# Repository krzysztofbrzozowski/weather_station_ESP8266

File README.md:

# Weather station based on ESP8266 and BME280
## Repository Contents

- **firmware/micropython/src/** - MicroPython files deployed to the ESP8266.
- **firmware/micropython/build/** - Generated MicroPython deployment files, ignored by Git.
- **firmware/.settings** - Shared private configuration for both firmware implementations.
- **firmware/arduino/** - Native C++ firmware using Arduino, BearSSL HTTPS and LittleFS;
  see its [build and migration guide](firmware/arduino/README.md).
- **local_dev/** - CPython launcher and runtime stubs for local development.
- **platformio.sh** - Build or flash Arduino with current shared settings and image verification.

The board currently runs Arduino. For settings, builds and uploads, use the
[Arduino guide](firmware/arduino/README.md#updating-settings-and-firmware).
The deployment instructions below describe MicroPython.

## Configuration

Both implementations use the shared host configuration `firmware/.settings`.
The local MicroPython launcher reads it directly; deployment copies it to
`/.settings` on the device. Arduino's preparation tool converts it into
`/config.json` for the device. Changing the host file alone does not update the board.
If it is missing, copy `firmware/.settings.example` to that path and edit it:

```python
API_url = 'Your API url'
AUTH_TOKENS = {
    'dc:4f:22:7c:3a:fa': 'Your-token-for-first-device',
    'dc:4f:22:7c:3a:fc': 'Your-token-for-second-device',
}
BACKUP_FOLDER = 'backup_logs'
WIFI_NETWORKS = [
    {'SSID': 'Home-WiFi', 'PASSWD': 'Your-home-password'},
    {'SSID': 'Office-WiFi', 'PASSWD': 'Your-office-password'},
]
```

The file uses Python assignments and is ignored by Git. `API_url` and
`BACKUP_FOLDER` are strings. `WIFI_NETWORKS` holds 1–4 SSID/password profiles;
the legacy `SSID` and `PASSWD` strings still work when the list is absent.
The list takes precedence over legacy credentials. Each SSID is 1–32 UTF-8
bytes, each password 0–64 bytes; an empty password selects an open network.
Exact duplicate profiles are rejected; the same SSID with different passwords
is allowed.

On first use, multi-network firmware scans for configured visible SSIDs and
tries them in list order. It saves the successful profile in `/.wifi.json`,
which survives deep sleep and power loss. Later cycles try that profile first;
if connection fails they scan again and try the other visible profiles. A scan
failure falls back to direct attempts. Only a changed successful preference is
written to flash. Changing credentials/order invalidates the saved preference.
If all networks fail, measurements stay queued and discovery retries next cycle.

`AUTH_TOKENS` maps Wi-Fi station MAC
addresses to their API tokens. Each board selects its token at startup; the same
settings file/image can be used on all boards. MACs are case insensitive and
accept colons or hyphens. Use 1–100 entries and 1–256 printable ASCII characters
per token, without spaces. Duplicate MACs after normalization are rejected.

An unknown MAC leaves uploads disabled while measurements remain queued and the
normal sleep cycle continues. The console reports the missing MAC, without
printing any tokens. The legacy single-device `AUTH_TOKEN = 'Your API token'`
format still works when `AUTH_TOKENS` is absent. A present map takes precedence;
there is no fallback to another device's token.

Optional numeric controls and their defaults are:

```python
MEASUREMENT_INTERVAL_S = 300
HTTP_TIMEOUT_S = 3
BACKUP_MAX_RECORDS = 144
BACKUP_MIN_FREE_BYTES = 32768
BACKUP_MAX_SEND = 6
```

`BACKUP_FOLDER` is a single directory name. Local development uses the same file even when launched from a
different working directory; backup files still go into the simulated device
filesystem. When using `local_dev/run.py`, HTTP and Wi-Fi remain simulated.
Use `local_dev/send_test_measurements.py` below for real HTTP requests.

The measurement interval accepts 10–3600 seconds and the HTTP timeout 1–3 seconds
to stay within the ESP8266's sleep timer and fixed watchdog constraints.

## Local development

Run from the repository root with Python 3 (standard library only):

```sh
python3 local_dev/run.py
```

The launcher executes `firmware/micropython/src/boot.py` and `firmware/micropython/src/main.py`, replacing
hardware and HTTP modules with runtime stubs. It supplies fixed BME280 readings,
an ADC value and a MAC address, simulates Wi-Fi and API responses, skips
millisecond delays, and finishes when the firmware enters deep sleep.
It does not send real HTTP requests or require Wi-Fi credentials.

To simulate unavailable Wi-Fi and exercise measurement backups:

```sh
python3 local_dev/run.py --offline
python3 local_dev/run.py
```

Simulated device files are stored in `local_dev/.state/` (ignored by Git).
The second command simulates sending up to `BACKUP_MAX_SEND` pending readings.
Simulated RTC state is retained in `.state/.rtc.json` between invocations.
Use `--state-dir /path/to/directory` to choose a different device filesystem.
Adjust simulated readings in `local_dev/stubs/` as needed.

These stubs support the interfaces currently used by the application. They
replace the BME280 driver entirely and do not verify I2C communication,
sensor calibration, real API compatibility, or ESP8266 timing and power behavior.

## Deployment

Build the modules from `firmware/micropython/src/` on the computer and upload the resulting
`.mpy` files, `boot.py`, `main.py` and the private `.settings` to the ESP8266 root
as shown below. Configure Wi-Fi and API settings in `.settings`.
The `local_dev/` directory stays on the development
computer and is not deployed to the board.

Use a MicroPython build for your exact ESP8266 board with a working `urequests`
or `requests` module supporting the `timeout` argument. Do not copy the local
stubs to the board. For resilience to interrupted writes, use a LittleFS
filesystem. Connect GPIO16 to RST for timed wakeup, connect BME280 SCL to GPIO5
and SDA to GPIO4, and confirm its I2C address is `0x76`.
The existing GPIO13 charging check and ADC divider scaling are preserved;
they must match your PCB. Test a complete sleep/wake cycle on the actual board.

### 1. Install the flashing tools

The commands below use **macOS/Linux**, Python **3.10+**, and the current
`esptool` command syntax. Run them from the repository root:

```sh
python3 -m venv .venv
source .venv/bin/activate
python -m pip install --upgrade esptool mpremote
```

`esptool` installs the MicroPython interpreter; `mpremote` transfers this
project's Python files afterwards. See the official
[esptool installation guide](https://docs.espressif.com/projects/esptool/en/latest/esp8266/installation.html).

### 2. Connect the board and identify its flash size

Use a USB data cable and close other serial terminals. List connected ports:

```sh
python -m serial.tools.list_ports
```

Set the actual port shown above (the following macOS name is an example;
Linux commonly uses `/dev/ttyUSB0`):

```sh
ESP_PORT='/dev/cu.usbserial-210'
python -m esptool --chip esp8266 --port "$ESP_PORT" flash-id
```

Read `Detected flash size` before choosing a firmware variant. Boards with an
automatic reset circuit usually enter the bootloader themselves. Otherwise,
hold **FLASH/BOOT** (GPIO0 low), press and release **RST**, and retry the command.
For a bare module, pull GPIO0 to GND while resetting; release GPIO0 for normal boot.

### 3. Download the latest stable MicroPython binary

Open the official [ESP8266 firmware downloads](https://micropython.org/download/ESP8266_GENERIC/)
and choose the newest `.bin` under **Releases** for your flash size. As of
**2026-10-14**, the latest stable release is **v1.29.0 (2026-08-24)**; check that
page again when installing later.

| Detected flash | Firmware choice |
| --- | --- |
| 2–4 MiB | Standard `ESP8266_GENERIC` build |
| 1 MiB | `FLASH_1M` variant; fewer bundled modules and less buffer space |
| 512 KiB | Unsuitable for this project: the current variant has no filesystem |
| 8–16 MiB | Standard build plus the [additional RF calibration procedure](https://docs.micropython.org/en/latest/esp8266/tutorial/intro.html#boards-with-more-than-4mb-of-flash) |

Use a release build for the station. Preview builds are development snapshots.
Rename your downloaded file to `micropython-esp8266.bin` and set its path:

```sh
MICROPYTHON_BIN="$HOME/Downloads/micropython-esp8266.bin"
```

### 4. Erase the old firmware and flash MicroPython

**Erasing removes everything on the board, including `.settings` and unsent
measurements.** Save anything you need before this step. The standard procedure
below covers boards with 1–4 MiB flash:

```sh
python -m esptool --chip esp8266 --port "$ESP_PORT" erase-flash
python -m esptool --chip esp8266 --port "$ESP_PORT" --baud 460800 write-flash --flash-size detect 0x0 "$MICROPYTHON_BIN"
```

The ESP8266 image starts at **`0x0`**. Current esptool uses names such as
`write-flash` and `erase-flash`; older tutorials use underscores.
If writing is unreliable, retry at `--baud 115200`. If flashing succeeds but
MicroPython does not boot, retry with the compatibility flash mode:

```sh
python -m esptool --chip esp8266 --port "$ESP_PORT" --baud 115200 write-flash --flash-size detect --flash-mode dout 0x0 "$MICROPYTHON_BIN"
```

Release FLASH/GPIO0 and press RST after flashing. Let the first boot initialize
the filesystem, then check the interpreter:

```sh
mpremote connect "$ESP_PORT" exec "import sys; print(sys.implementation)"
```

Command references: [MicroPython ESP8266 installation](https://docs.micropython.org/en/latest/esp8266/tutorial/intro.html)
and [esptool flash commands](https://docs.espressif.com/projects/esptool/en/latest/esp8266/esptool/basic-commands.html).

### 5. Prepare settings and the HTTP library

Create `firmware/.settings` from `.settings.example` **only if it does not
already exist**, then enter the actual API and Wi-Fi settings in your editor.
Keep an existing private configuration when updating.

```sh
test -f firmware/.settings || cp firmware/.settings.example firmware/.settings
mpremote connect "$ESP_PORT" mip install requests
mpremote connect "$ESP_PORT" exec "import requests; print('HTTP library available')"
```

Installing `requests` uses the computer's Internet connection and USB transfer;
the board does not need to join Wi-Fi for this step. The firmware supports
`urequests` as well. If an older copy of `urequests.py` was previously uploaded,
update or remove that obsolete copy so it does not shadow the current library.
See [MicroPython package installation](https://docs.micropython.org/en/latest/reference/packages.html#installing-packages-with-mpremote).

### 6. Upload the station code

ESP8266 has limited RAM. Compiling all source modules on the device can fail
with `MemoryError` even when the files fit in flash. Precompile the importable
modules on the computer, using an `mpy-cross` release matching the board's
MicroPython version. For **MicroPython 1.29.0**:

```sh
python -m pip install 'mpy-cross==1.29.0.post2'
python local_dev/build_firmware.py
```

The build goes into `firmware/micropython/build/` (ignored by Git). Entry points `boot.py`
and `main.py` stay as Python source; the other modules become `.mpy` files.
The builder does not copy private settings. See
[MicroPython RAM and precompilation](https://docs.micropython.org/en/latest/reference/constrained.html#compilation-phase)
and [.mpy version compatibility](https://docs.micropython.org/en/latest/reference/mpyfiles.html).

Upload the build and explicitly include the hidden `.settings`:

```sh
mpremote connect "$ESP_PORT" fs cp firmware/micropython/build/APIrequests.mpy firmware/micropython/build/BME280.mpy firmware/micropython/build/backup.mpy firmware/micropython/build/settings.mpy firmware/micropython/build/station_clock.mpy firmware/micropython/build/station_wifi.mpy firmware/micropython/build/boot.py firmware/micropython/build/main.py firmware/.settings :/
```

If the older `.py` modules from this project are already on the device, remove
**those source copies only after their `.mpy` replacements upload successfully**:

```sh
mpremote connect "$ESP_PORT" fs rm :APIrequests.py :BME280.py :backup.py :settings.py :station_clock.py :station_wifi.py
```

Skip that removal command on a clean installation. Keep `main.py`, `boot.py`,
`.settings`, `lib/` and measurement backups. Then verify the installed modules:

```sh
mpremote connect "$ESP_PORT" exec "import APIrequests, BME280, backup, settings, station_clock, station_wifi; settings.load_settings(); print('Firmware imports and settings OK')"
mpremote connect "$ESP_PORT" fs ls
```

The loader supports ESP8266 builds which omit `__file__`: it reads `/.settings`
on the board and the shared `firmware/.settings` during local development.

Do not upload `local_dev/`, its stubs, or `.settings.example`. Confirm the BME280
is visible before starting the application; its default address should be `0x76`:

```sh
mpremote connect "$ESP_PORT" exec "from machine import Pin, I2C; print([hex(a) for a in I2C(scl=Pin(5), sda=Pin(4), freq=10000).scan()])"
```

### 7. Start the station and check one complete cycle

```sh
mpremote connect "$ESP_PORT" repl
```

Press **Ctrl+D** in the REPL to restart MicroPython and run `main.py`. Watch the
measurement/backup messages, then verify that the station wakes for the next
cycle (five minutes by default). Output pauses during deep sleep. GPIO16 must
be connected to RST for timed wakeup. Press **Ctrl+]** to leave the terminal.
For later source updates, repeat the upload step; erasing the flash is only
needed for a clean interpreter installation and would delete pending readings.
See the [mpremote manual](https://docs.micropython.org/en/latest/reference/mpremote.html).

To enter REPL while the station is running, connect the terminal first, press the
physical **RST** button, then press **Ctrl+C** when you see
`Service window: press Ctrl+C within 3 s to enter REPL`. This leaves you at `>>>`
before the hardware watchdog is enabled. **Ctrl+D** starts the firmware again.
Interrupting an active measurement cycle instead requests a hardware reset;
press **Ctrl+C** again during the service window to enter REPL. Timed deep-sleep
wakes and watchdog recovery skip this window. An already sleeping chip cannot
receive Ctrl+C: use RST to wake it before trying to interrupt startup.

This service window requires the updated `main.py` on the device. After building,
upload `firmware/micropython/build/main.py` using the upload instructions above. This does
not require erasing flash or reinstalling MicroPython.

Keep the terminal at **115200 baud** for REPL and application messages. ESP8266
ROM startup messages normally use **74880 baud**, so some unreadable characters
around reset are expected at the REPL speed; see the
[Espressif boot log reference](https://docs.espressif.com/projects/esptool/en/latest/esp8266/advanced-topics/boot-mode-selection.html#boot-log).

For the custom weather-station PCB, close **SJ2** to connect the `WAKE` net (GPIO16) to
`RST`. An open SJ2 prevents timed deep-sleep wake unless another physical
connection provides that path. A restart seen while opening/closing a USB serial
terminal is not proof of timed wake: the adapter can toggle reset control lines.

To check wake without reopening the port, use the host-side diagnostic (with the
current `main.py` installed so it prints the reset cause):

```sh
python local_dev/check_device_sleep.py --port "$ESP_PORT" --seconds 10
```

It keeps the serial connection open throughout sleep and requires a delayed
boot with `machine.DEEPSLEEP_RESET`. If the device is already asleep and cannot
enter the REPL, reset it before starting the diagnostic. A timeout with the
sleep command confirmed means automatic wake was not observed; do not interpret
it as a successful test. This check does not measure sleep current.
To catch a manual reset while keeping USB connected, start it with
`--wait-for-reset 120`, then press RST while the script is waiting.

If the firmware reports **HTTP 401**, register the physical device's MAC address
on the server and use that sensor's token. To read the MAC without showing secrets:

```sh
mpremote connect "$ESP_PORT" exec "import network, ubinascii; print(ubinascii.hexlify(network.WLAN(network.STA_IF).config('mac'), ':').decode())"
```

Rejected authentication leaves measurements in the offline buffer. Once the
MAC/token configuration is corrected, later cycles retry those records.

## Offline buffer and recovery

The station saves each valid measurement **before** attempting HTTP, even while
online. It uses an oldest-first bounded queue of independent JSON files, with
sequence filenames that do not depend on the clock. By default it retains at
most **144 readings** (about 12 hours at five-minute intervals, if space permits).
It removes the oldest queued readings when this limit or the free-space reserve
is reached. It only evicts recognized measurement files in `BACKUP_FOLDER`.
If other files consume all available space, the station stops writing backups
and still attempts to send the current reading when Wi-Fi is available.

Each update is written to a temporary file, closed, synced and renamed. On boot,
complete interrupted writes are recovered and incomplete temporary files are
discarded. A corrupt record does not block the remaining queue. This depends on
the underlying filesystem and does not replace hardware power-loss testing.
JSON keeps records inspectable and independently recoverable; pickle adds no
useful benefit for this small, fixed measurement payload. Actual disk usage
depends on filesystem allocation blocks, so eviction may occur before 144 files.

The timestamp is captured at measurement time and persisted before the first
POST. Retries send the same payload and timestamp; the API must accept identical
replays idempotently. HTTP errors, timeouts and lost responses retain the record.
Uploads stop on connection failures, authentication failures, rate limiting or
server errors. Permanently rejected records (400/409/422) stay in the buffer
marked as rejected and are skipped on subsequent cycles, until oldest-first
eviction. Uploads have both a request-count limit and an elapsed-time budget.

RTC memory tracks clock continuity through deep sleep. Readings collected before
the first successful time sync are converted using their captured RTC seconds,
not their position in the queue. A small `.clock-session` marker ties RTC state
to the filesystem: erasing/reflashing the filesystem invalidates retained RTC
metadata, so the first measurement is synchronized again instead of trusting an
old clock. The conversion is also saved to disk so that an
interrupted upload can resume after power loss. If power is lost **before any
successful time sync**, absolute times for that earlier RTC session cannot be
reconstructed: those records are retained until buffer eviction and are not
uploaded with invented dates. Previously timestamped readings remain sendable.
Legacy date-named `.txt` backups with valid timestamps are also supported.

Single-network MicroPython connects immediately and defaults to an eight-second
wait. `WIFI_TIMEOUT_S` changes the wait per profile (1–30 seconds); multi-network
discovery and attempts share a 45-second overall limit. HTTP uses the
configured socket timeout; DNS and a stuck native operation are also covered by
the hardware watchdog, which resets the board if execution stops progressing.
After a watchdog reset the next boot sleeps for one interval before retrying,
so a permanently stuck connection does not cause a rapid reset loop.
Sensor conversion has a one-second limit. Handled failures, including sensor,
configuration and storage errors, reach deep sleep. Awake time is subtracted
from the measurement interval instead of adding an arbitrary eight seconds.

## Observatory camera-server integration

The station can also send readings to the `remote_surv_camera.nosync` server.
Create a sensor in that server's Django Admin, register this station's MAC,
assign readers and copy its per-device token. In `firmware/.settings`, set
`API_url = 'https://YOUR-SERVER/api/measurements'` (no trailing slash) and
the corresponding `AUTH_TOKENS` entry (or legacy `AUTH_TOKEN`) to that sensor's
token. The endpoint accepts the existing
BME280 payload and provides `/timesync` and `/timedelta/<seconds>` in UTC.
See `remote_surv_camera.nosync/docs/climate.md` for setup and API details.

The updated `APIrequests.py` raises on unsuccessful HTTP responses and closes
responses even on errors. This keeps backup files until the server accepts
them, including when authentication fails or the server rate-limits requests.
Copy this updated file to the board as part of deployment.

Run the HTTP-error and backup-retention checks without hardware or networking:

```sh
python3 -m unittest discover -s local_dev -p 'test_*.py'
```

## Send 10 readings to the real API

`local_dev/run.py` simulates HTTP and does **not** send anything to the server.
Use the separate smoke test for real HTTP requests, without an ESP8266:

```sh
python3 local_dev/send_test_measurements.py --mac aa:bb:cc:dd:ee:ff
```

Replace the MAC with the exact address registered in **Admin > Sensors**.
The script reads `API_url` and selects the token for `--mac` from `AUTH_TOKENS`
(or reads the legacy `AUTH_TOKEN`) in the private
`firmware/.settings` file; Wi-Fi credentials are not used or displayed.
Use `--settings /path/to/.settings` for another configuration.

By default, it sends **10 synthetic temperatures from 20.0 to 24.5 degrees C**,
spaced five minutes apart over the last 45 minutes. It synchronizes with the
server clock, validates each saved ID and timestamp, and stops on the first
failure with a nonzero exit code. HTTP 201 means a new reading; HTTP 200 means
an identical reading was already saved. Check **Climate > 24 h** for the trend.
These test readings are stored in the selected sensor's real history.
For separate test data, provision a dedicated sensor with its own MAC and token.

Preview all payloads without making network requests:

```sh
python3 local_dev/send_test_measurements.py --mac aa:bb:cc:dd:ee:ff --dry-run
```

Optional controls: `--count 10`, `--temperature 20`, `--temperature-step 0.5`,
`--step-seconds 300`, `--delay 0.25`, `--timeout 10`.
The script uses only the Python standard library, does not print tokens,
does not execute the configuration file, and refuses HTTP redirects.

## Publishing source

Commit `.settings.example` with placeholder values. Keep your real `.settings`,
`.env` files, backups and local runtime state out of Git. The ignore rules cover
these files, but do not remove files that were already tracked; review
`git status` and the staged diff before publishing. If a credential was ever
committed, ignoring its file later does not remove it from history: rotate it
before sharing that history.

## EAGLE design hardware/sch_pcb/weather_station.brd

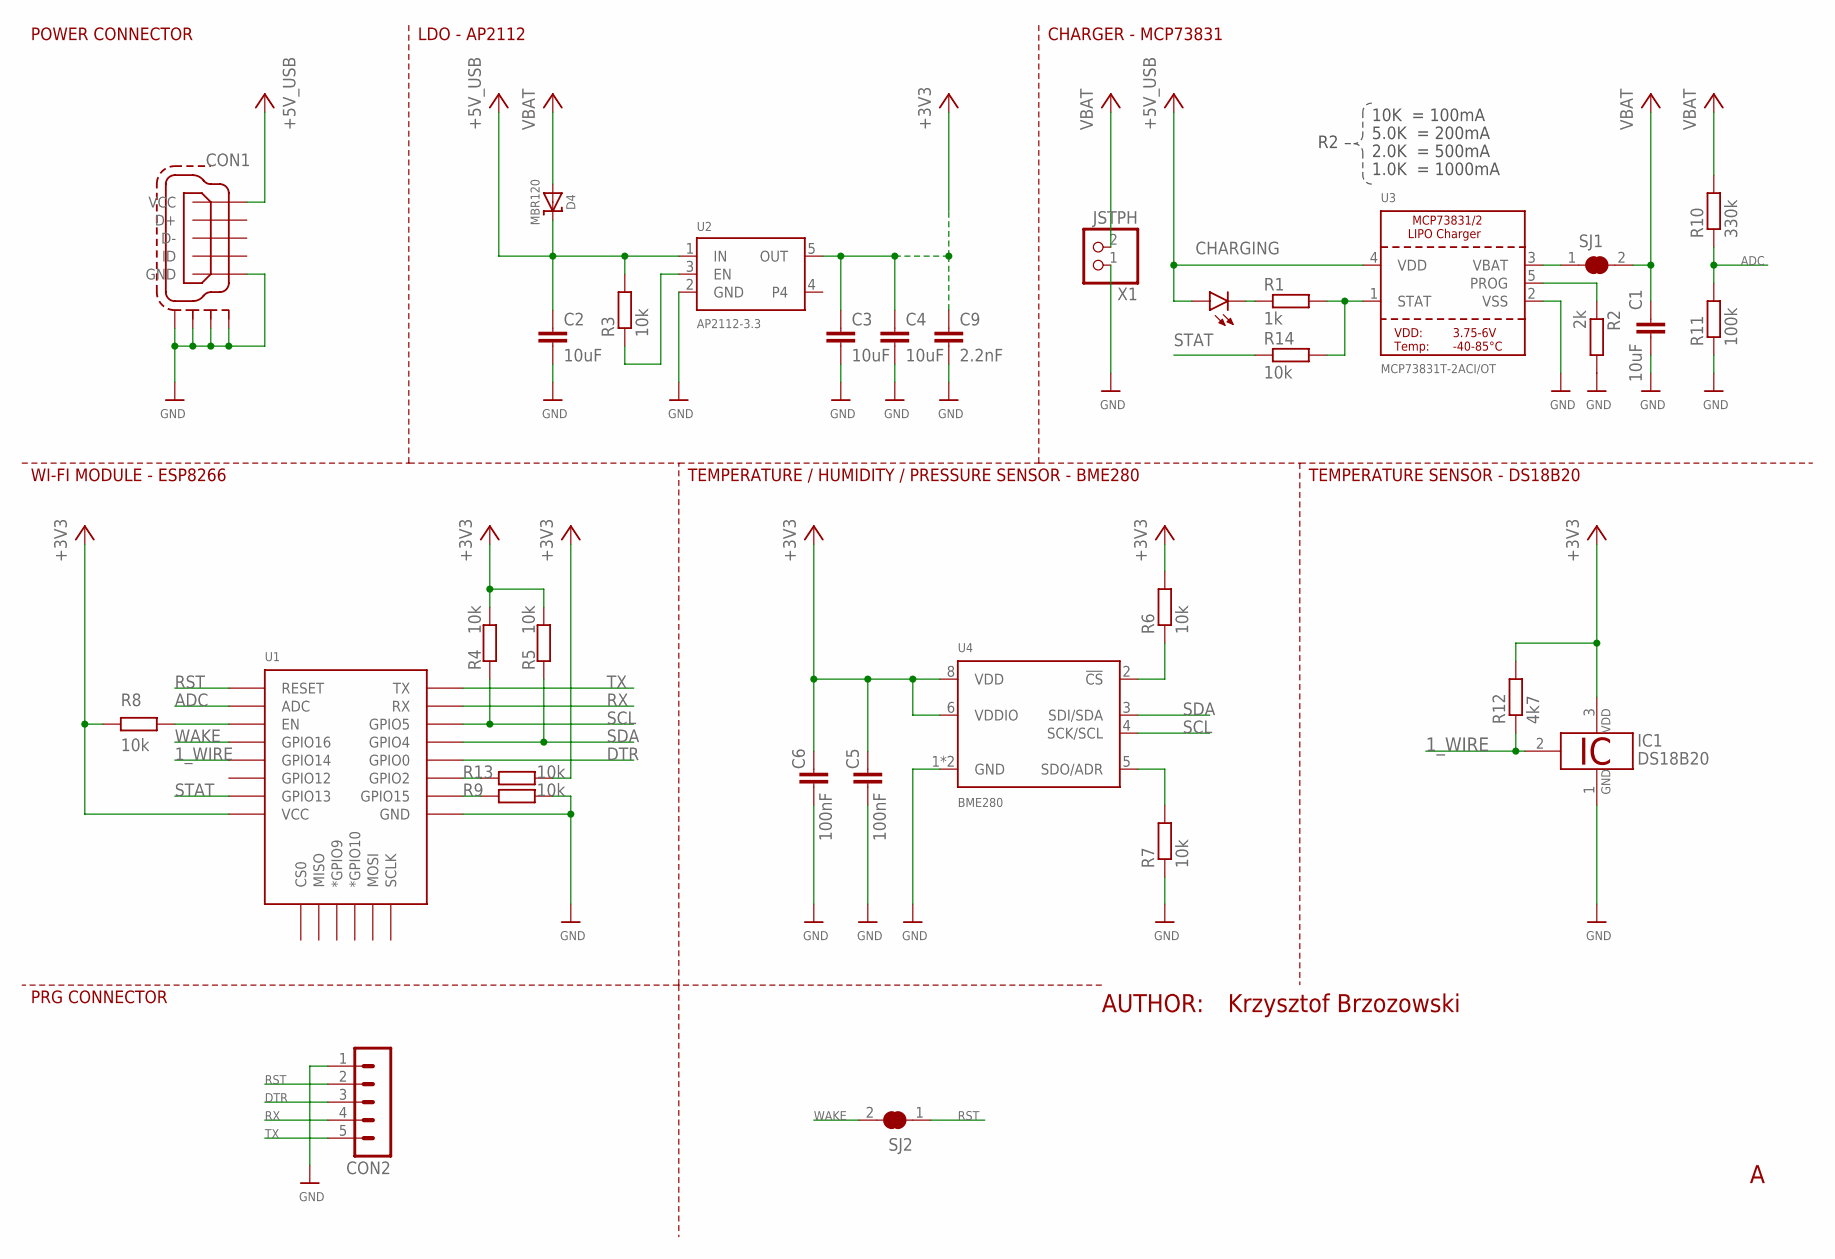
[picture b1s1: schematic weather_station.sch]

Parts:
C1, C2, C3, C4: 10uF; C1210
C5, C6: 100nF; C0402K
C9: 2.2nF; C0402K
CHARGING: LEDCHIPLED_0603; CHIPLED_0603
CON1: MICROUSB-MOLEX
CON2: MA05-1
D4: MBR120; SOD-123
IC1: DS18B20; TO92-LNG
R1: 1k; R0402
R2: 2k; R0402
R3, R4, R5, R6, R7, R8, R9, R13, R14: 10k; R0402
R10: 330k; R0402
R11: 100k; R0402
R12: 4k7; R0402
SJ1, SJ2: SOLDERJUMPER_CLOSED; SOLDERJUMPER_CLOSEDWIRE
U1: ESP12ESMD; ESP12E-SMD
U2: AP2112-3.3; SOT23-5
U3: MCP73831T-2ACI/OT; SOT23-5
U4: BME280; LGA-8-2.5X2.5
X1: JSTPH; JSTPH2

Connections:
1_WIRE: IC1.2 (1W), R12.1, U1.GPIO14
+3V3: C3.1, C4.1, C5.1, C6.1, C9.1, IC1.3 (VDD), R4.2, R5.2, R6.2, R8.2, R12.2, R13.1, U1.VCC, U2.5 (OUT), U4.6 (VDDIO), U4.8 (VDD)
+5V_USB: C2.1, CHARGING.A, CON1.VCC, D4.C, R3.2, U2.1 (IN), U3.4 (VDD)
ADC: R10.1, R11.2, U1.ADC
DTR: CON2.3, U1.GPIO0
EN: R3.1, U2.3 (EN)
GND: C1.2, C2.2, C3.2, C4.2, C5.2, C6.2, C9.2, CON1.GND, CON1.GND_H_00 (SH1), CON1.GND_H_01 (SH2), CON1.GND_H_02 (SH3), CON1.GND_H_03 (SH3), CON1.GND_H_04 (SH3), CON1.GND_H_05 (SH3), CON1.GND_H_06 (SH3), CON1.GND_H_07 (SH3), CON1.GND_H_08 (SH3), CON1.GND_H_09 (SH3), CON1.GND_H_10 (SH3), CON1.GND_H_11 (SH3), CON1.GND_H_12 (SH3), CON1.GND_H_13 (SH4), CON1.GND_H_14 (SH4), CON1.GND_H_15 (SH4), CON1.GND_H_16 (SH4), CON1.GND_H_17 (SH4), CON1.GND_H_18 (SH4), CON1.GND_H_19 (SH4), CON1.GND_H_20 (SH4), CON1.GND_H_21 (SH4), CON1.GND_H_22 (SH4), CON1.GND_H_23 (SH4), CON1.GND_P_0 (SH3), CON1.GND_P_1 (SH3), CON1.GND_P_2 (SH4), CON1.GND_P_3 (SH4), CON2.1, IC1.1 (GND), R2.2, R7.1, R9.1, R11.1, U1.GND, U2.2 (GND), U3.2 (VSS), U4.1 (GND), U4.7 (GND), X1.1
unnamed: CHARGING.C, R1.1
unnamed: SJ1.1, U3.3 (VBAT)
unnamed: R1.2, R14.2, U3.1 (STAT)
unnamed: R2.1, U3.5 (PROG)
unnamed: R6.1, U4.2 (!CS)
unnamed: R7.2, U4.5 (SDO/ADR)
unnamed: R13.2, U1.GPIO2
unnamed: R8.1, U1.CH_PD (EN)
unnamed: R9.2, U1.GPIO15
RST: CON2.2, SJ2.1, U1.RESET
RX: CON2.4, U1.RXD0 (RX)
SCL: R4.1, U1.GPIO5, U4.4 (SCK/SCL)
SDA: R5.1, U1.GPIO4, U4.3 (SDI/SDA)
STAT: R14.1, U1.GPIO13
TX: CON2.5, U1.TXD0 (TX)
VBAT: C1.1, D4.A, R10.2, SJ1.2, X1.2
WAKE: SJ2.2, U1.GPIO16

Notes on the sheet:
10K = 100mA
5.0K = 200mA
2.0K = 500mA
1.0K = 1000mA
AUTHOR:
Krzysztof Brzozowski
TEMPERATURE / HUMIDITY / PRESSURE SENSOR - BME280
POWER CONNECTOR
LDO - AP2112
CHARGER - MCP73831
WI-FI MODULE - ESP8266
TEMPERATURE SENSOR - DS18B20
PRG CONNECTOR

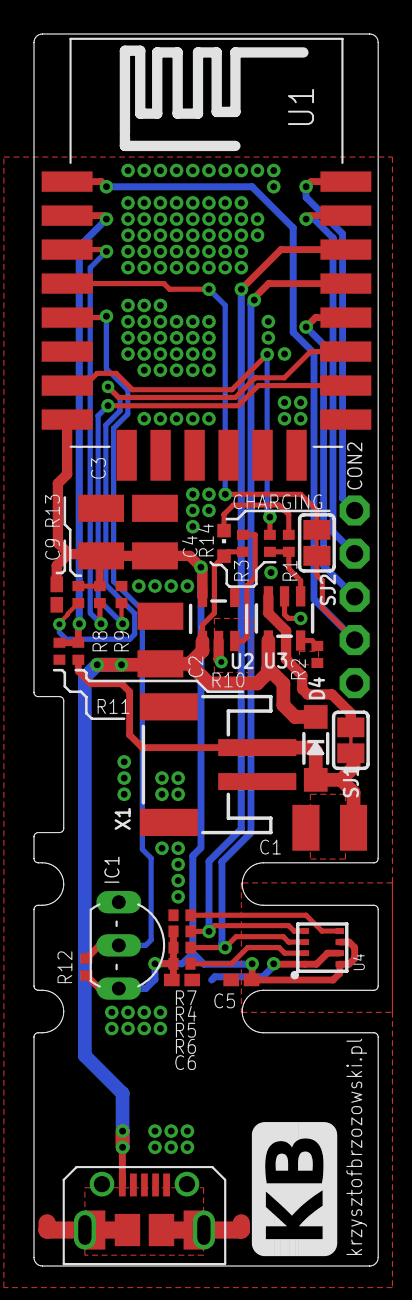
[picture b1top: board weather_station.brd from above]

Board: 2 copper layers, 20.2 x 72.5 mm, 33 parts (0 on the bottom side), 24 nets.

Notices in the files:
parts and their libraries:
microbuilder: This work is placed in the public domain, and may be freely used for commercial and non-commercial work with the following conditions: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
SparkFun-Sensors: Licensing: CC v3.0 Share-Alike You are welcome to use this library for commercial purposes.
